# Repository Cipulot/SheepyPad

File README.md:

# SheepyPad

SheepyPad is an ISO Enter shaped macropad easy to build and customize.

Main features included:

- 5x4 key matrix (both 3-pin and 5-pin supported)
- 128x32 OLED display for status indication
- Rotary encoder for media control
- Integrated 2 operand calculator with basic math operations (+, -, *, /, sqrt)
- VIA and QMK compatibility
- 6 addressable RGB LEDs for underglow

This board fully supports QMK and VIA. For QMK refer to the [official docs](https://beta.docs.qmk.fm/). If you wanna use VIA follow the instructions [here](https://github.com/Cipulot/SheepyPad/blob/main/Documents/via.md).

Follow the [PCB Assembly Instructions](https://github.com/Cipulot/SheepyPad/blob/main/Documents/pcb_assembly.md) to build the PCB and test it out.

## Repo structure

- `Docs` contains all documentation and images for the project.
- `Firmware` contains both the source and precompiled binaries.
- `Hardware` contains the KiCad design files for the keyboard, fabrication files and STEP file.

## Project status

Project is currently in development. V1 boards have been produced and tested succesfuly. V2 boards are in the works and will add/change currently available features (both hardware and firmware wise).

Software is in constant change and being updated on my qmk_firmware fork available [here](https://github.com/Cipulot/qmk_firmware). You can find a basic default code example (with precompiled binaries) in this repo too if you want to quickly get it up and running.

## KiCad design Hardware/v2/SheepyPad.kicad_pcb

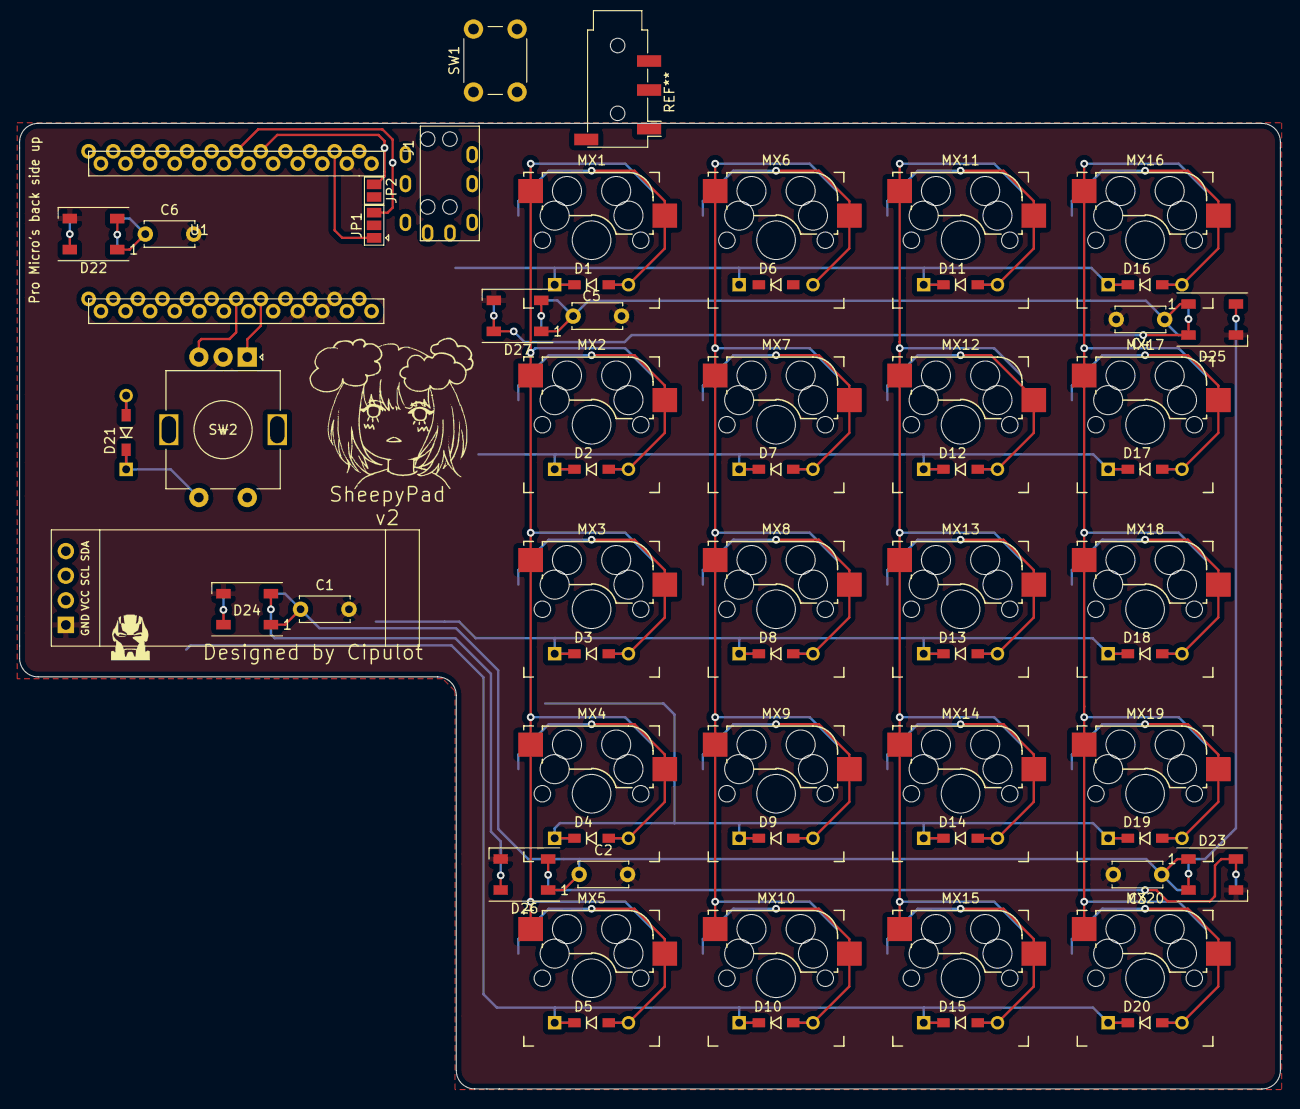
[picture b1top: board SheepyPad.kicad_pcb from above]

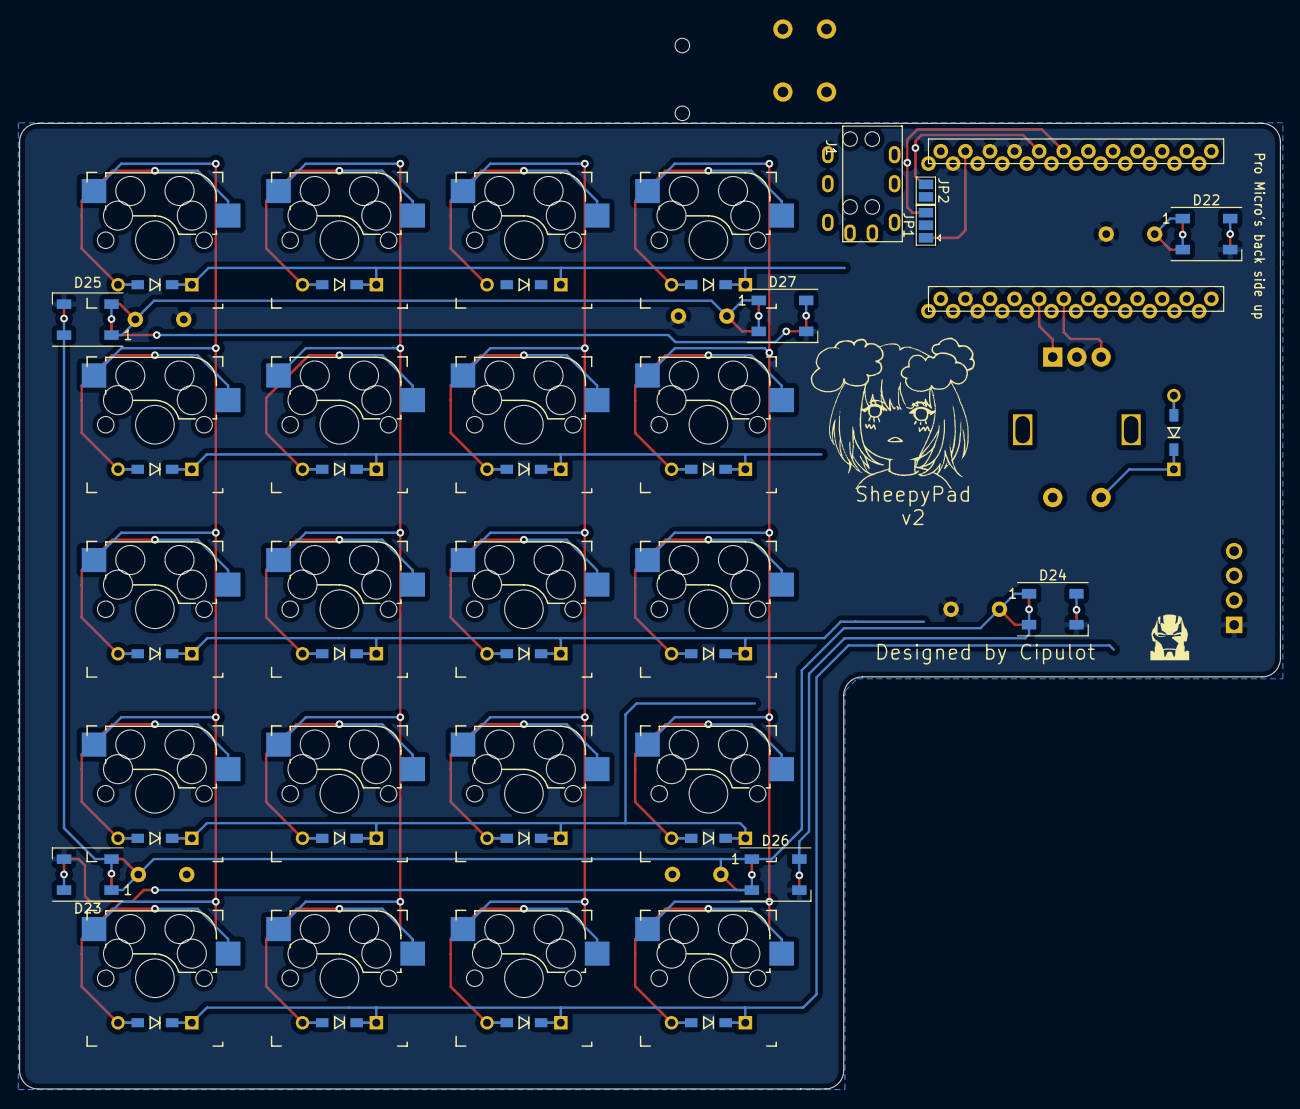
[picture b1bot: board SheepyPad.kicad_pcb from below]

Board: 2 copper layers, 130.2 x 99.7 mm, 69 parts (9 on the bottom side), 46 nets.

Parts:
Brd1: SSD1306; SSD1306-0.91-OLED-4pin-128x32
C1, C2, C3, C4, C5, C6: 100n; C_Disc_D5.0mm_W2.5mm_P5.00mm
D1, D2, D3, D4, D5, D6, D7, D8, D9, D10, D11, D12, D13, D14, D15, D16, D17, D18, D19, D20, D21: D_Small; Diode_SMD_THT_DUAL
D22, D22#2, D23, D23#2, D24, D24#2, D25, D25#2, D26, D26#2, D27, D27#2: WS2812B; LED_WS2812B_PLCC4_5.0x5.0mm_P3.2mm
J1, J1#2: AudioJack4; PJ-3200B-4A
JP1, JP1#2: Serial/SCL Jumper; SolderJumper-3_P1.3mm_Open_Pad1.0x1.5mm
JP2, JP2#2: SDA Jumper; SolderJumper-2_P1.3mm_Open_Pad1.0x1.5mm
MX1, MX2, MX3, MX4, MX5, MX6, MX7, MX8, MX9, MX10, MX11, MX12, MX13, MX14, MX15, MX16, MX17, MX18, MX19, MX20: MX-NoLED; Kailh_socket_MX_optional_reversible_FLIP
SW1: SW_Push; SW_PUSH_6mm
SW2: Rotary_Encoder_Switch; RotaryEncoder_Alps_EC11E-Switch_Vertical_H20mm
U1: Sparkfun_Pro_Micro; Sparkfun_Pro_Micro_reversible

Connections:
/COL_0: D21.2, U1.13
/COL_1: MX1.1, MX2.1, MX3.1, MX4.1, MX5.1, U1.14
/COL_2: MX6.1, MX7.1, MX8.1, MX9.1, MX10.1, U1.15
/COL_3: MX11.1, MX12.1, MX13.1, MX14.1, MX15.1, U1.16
/COL_4: MX16.1, MX17.1, MX18.1, MX19.1, MX20.1, U1.17
/DATA: JP1#2.1, U1.2
/ENC_A: SW2.A, U1.20
/ENC_B: SW2.B, U1.19
/GLOW_LED: D22.4, D22#2.4, U1.7
/RESET: SW1.2, U1.22
/ROW_0: D1.1, D6.1, D11.1, D16.1, SW2.S2, U1.12
/ROW_1: D2.1, D7.1, D12.1, D17.1, U1.11
/ROW_2: D3.1, D8.1, D13.1, D18.1, U1.10
/ROW_3: D4.1, D9.1, D14.1, D19.1, U1.9
/ROW_4: D5.1, D10.1, D15.1, D20.1, U1.8
/SCL: Brd1.3, JP1#2.3, U1.6
/SDA: Brd1.4, JP2#2.1, U1.5
GND: Brd1.1, C1.2, C2.2, C3.2, C4.2, C5.2, C6.2, D22.3, D22#2.3, D23.3, D23#2.3, D24.3, D24#2.3, D25.3, D25#2.3, D26.3, D26#2.3, D27.3, D27#2.3, SW1.1, SW2.C, U1.3, U1.4, U1.23
unnamed: D1.2, MX1.2
unnamed: D2.2, MX2.2
unnamed: D3.2, MX3.2
unnamed: D4.2, MX4.2
unnamed: D5.2, MX5.2
unnamed: D6.2, MX6.2
unnamed: D7.2, MX7.2
unnamed: D8.2, MX8.2
unnamed: D9.2, MX9.2
unnamed: D10.2, MX10.2
unnamed: D11.2, MX11.2
unnamed: D12.2, MX12.2
unnamed: D13.2, MX13.2
unnamed: D14.2, MX14.2
unnamed: D15.2, MX15.2
unnamed: D16.2, MX16.2
unnamed: D17.2, MX17.2
unnamed: D18.2, MX18.2
unnamed: D19.2, MX19.2
unnamed: D20.2, MX20.2
unnamed: D21.1, SW2.S1
unnamed: D22.2, D22#2.2, D24.4, D24#2.4
unnamed: D23.2, D23#2.2, D25.4, D25#2.4
unnamed: D23.4, D23#2.4, D26.2, D26#2.2
unnamed: D24.2, D24#2.2, D26.4, D26#2.4
unnamed: D25.2, D25#2.2, D27.4, D27#2.4
unnamed: D27.2, D27#2.2
VCC: Brd1.2, C1.1, C2.1, C3.1, C4.1, C5.1, C6.1, D22.1, D22#2.1, D23.1, D23#2.1, D24.1, D24#2.1, D25.1, D25#2.1, D26.1, D26#2.1, D27.1, D27#2.1, U1.21

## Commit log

2021-09-14 Initialized and added project
2021-09-14 Add submodules
2021-09-14 Add project specific lib in KiCad project
2021-09-14 Gerber files output
2021-09-15 Various Updates
2021-09-15 Changes
    - Updated silkscreen logos
    - Updated tracks
2021-09-16 Updates
    - Updates nets (again)
    - Updated gerber files for production
2021-09-25 Update fabrication
2021-09-27 Repo formatting
    Added folder in prevision of future additions
2021-09-28 Fixed Diode orientation for encoder SW
2021-09-28 Changes to config.h and keymap
    config.h : removed all animations in favour of single ones
    keymap: added custom logo badge for oled
2021-10-02 Various changes
    info.json: Modified keymap layout for proper VIA recognition.
    sheepypad.h: modified LAYOUT to reflect matrix wiring and blanks.
    keymap.c: fixed keymap and added primitive calculator features
2021-10-23 Code update
2021-10-23 Boards images upload
2021-10-23 Compiled binary file
2021-10-23 Resized images
2021-10-23 File name change
2021-10-26 Moved file around
2021-10-26 Removed zip file to offload data usage
2021-10-26 Rename README.md to Readme.md
2021-10-26 Set theme jekyll-theme-hacker
2021-10-26 Update Readme.md
    Grammar check
2021-10-26 Set theme jekyll-theme-cayman
2021-10-27 Update Readme.md
    Typo fix
2021-10-27 Update calculator.md
    Added image and missing operation from prev commit
2021-10-27 Update calc.c
    Added 2 operand support for `SQRT` function
2021-10-27 Update calculator.md
    Update of documentation after addition in #09257b9
2021-10-27 Addition of function to handle result print
2021-10-27 Added operation handling function (free space)
2021-11-04 File move for v2
2021-11-04 Add of personal KiCad submodule
2021-11-04 Remove of redundant lib
2021-11-05 WIP v2
2021-11-05 Removed submodules
    Submodules have being replaced with personal collection in another submodule. Therefore there's no need to keed a copy of them.
2021-11-05 Update Submodule
2021-11-05 Update v2
2021-11-05 PCB update
2021-11-05 Update from qmk fork
2021-11-07 Update of submodule
2021-11-08 Update cipulot_kicad_parts
